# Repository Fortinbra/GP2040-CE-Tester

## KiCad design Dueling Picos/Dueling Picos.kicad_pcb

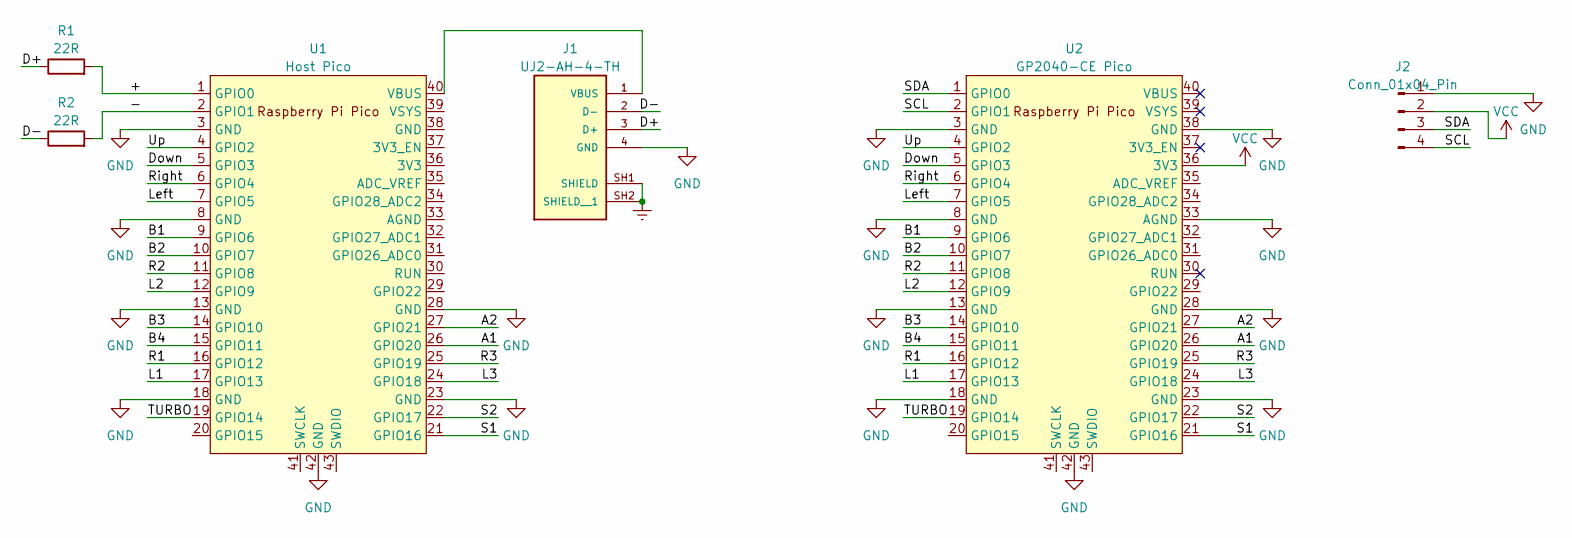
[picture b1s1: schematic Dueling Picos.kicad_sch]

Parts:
J1: UJ2-AH-4-TH; CUI_UJ2-AH-4-TH; PART_REV 1.0
J2: Conn_01x04_Pin; JST_SH_BM04B-SRSS-TB_1x04-1MP_P1.00mm_Vertical
R1, R2: 22R; R_0201_0603Metric
U1: Host Pico; RPi_Pico_SMD_TH
U2: GP2040-CE Pico; RPi_Pico_SMD_TH

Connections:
/+: R1.2, U1.1 (GPIO0)
/-: R2.2, U1.2 (GPIO1)
/A1: U1.26 (GPIO20), U2.26 (GPIO20)
/A2: U1.27 (GPIO21), U2.27 (GPIO21)
/B1: U1.9 (GPIO6), U2.9 (GPIO6)
/B2: U1.10 (GPIO7), U2.10 (GPIO7)
/B3: U1.14 (GPIO10), U2.14 (GPIO10)
/B4: U1.15 (GPIO11), U2.15 (GPIO11)
/D+: J1.3 (D+), R1.1
/D-: J1.2 (D-), R2.1
/Down: U1.5 (GPIO3), U2.5 (GPIO3)
/L1: U1.17 (GPIO13), U2.17 (GPIO13)
/L2: U1.12 (GPIO9), U2.12 (GPIO9)
/L3: U1.24 (GPIO18), U2.24 (GPIO18)
/Left: U1.7 (GPIO5), U2.7 (GPIO5)
/R1: U1.16 (GPIO12), U2.16 (GPIO12)
/R2: U1.11 (GPIO8), U2.11 (GPIO8)
/R3: U1.25 (GPIO19), U2.25 (GPIO19)
/Right: U1.6 (GPIO4), U2.6 (GPIO4)
/S1: U1.21 (GPIO16), U2.21 (GPIO16)
/S2: U1.22 (GPIO17), U2.22 (GPIO17)
/SCL: J2.4, U2.2 (GPIO1)
/SDA: J2.3, U2.1 (GPIO0)
/TURBO: U1.19 (GPIO14), U2.19 (GPIO14)
/Up: U1.4 (GPIO2), U2.4 (GPIO2)
Earth: J1.SH1 (SHIELD), J1.SH2 (SHIELD__1)
GND: J1.4 (GND), J2.1, U1.3 (GND), U1.8 (GND), U1.13 (GND), U1.18 (GND), U1.23 (GND), U1.28 (GND), U1.42 (GND), U2.3 (GND), U2.8 (GND), U2.13 (GND), U2.18 (GND), U2.23 (GND), U2.28 (GND), U2.33 (AGND), U2.38 (GND), U2.42 (GND)
unnamed: J1.1 (VBUS), U1.40 (VBUS)
VCC: J2.2, U2.36 (3V3)

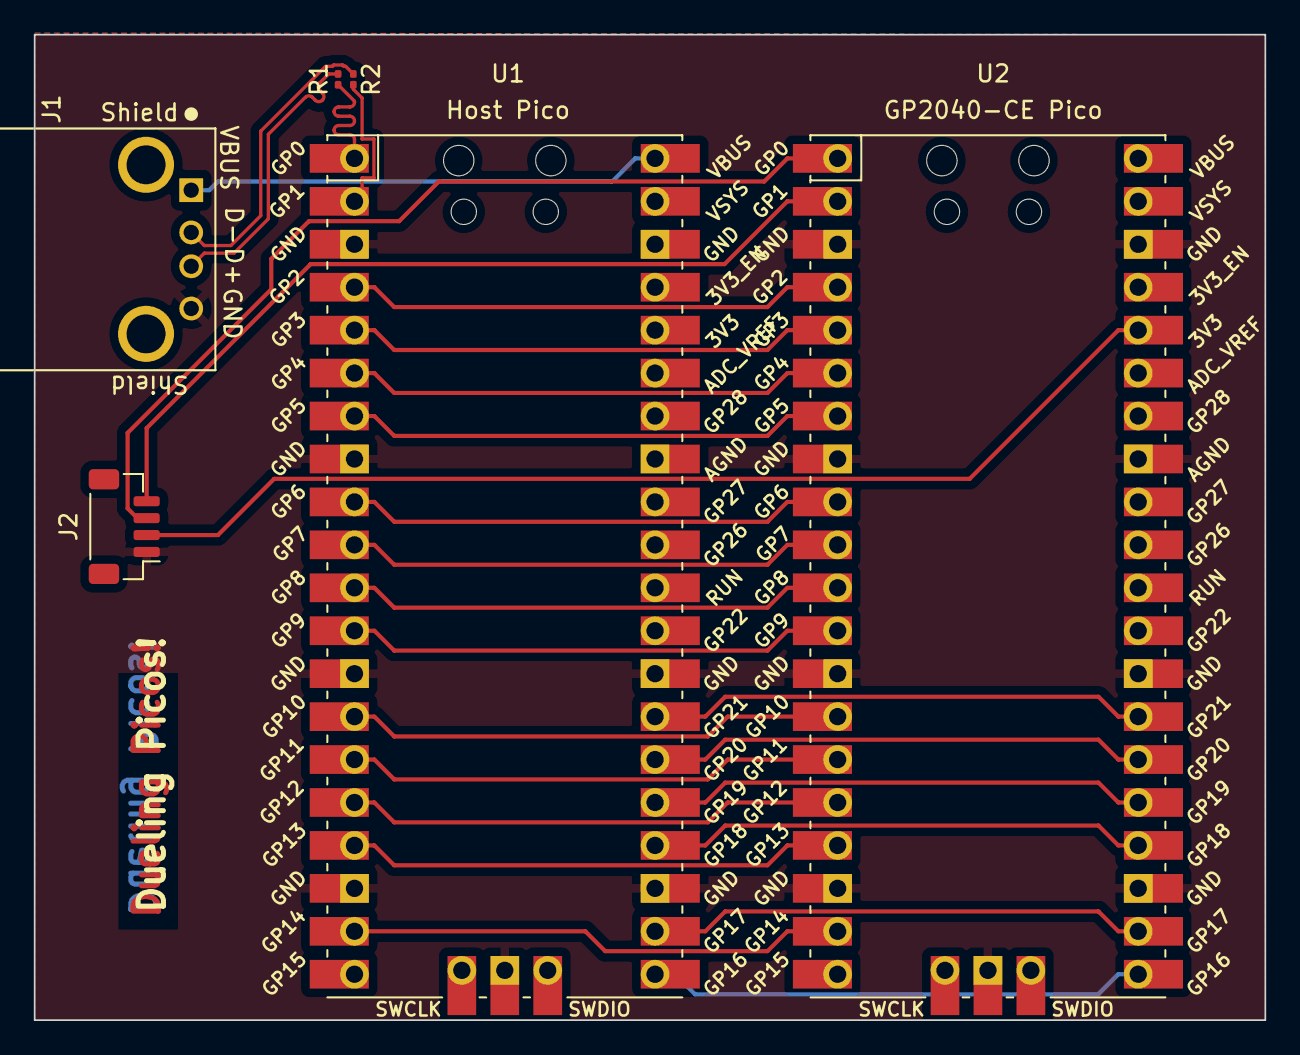
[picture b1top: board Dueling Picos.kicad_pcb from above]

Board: 2 copper layers, 72.8 x 58.3 mm, 6 parts (0 on the bottom side), 29 nets.

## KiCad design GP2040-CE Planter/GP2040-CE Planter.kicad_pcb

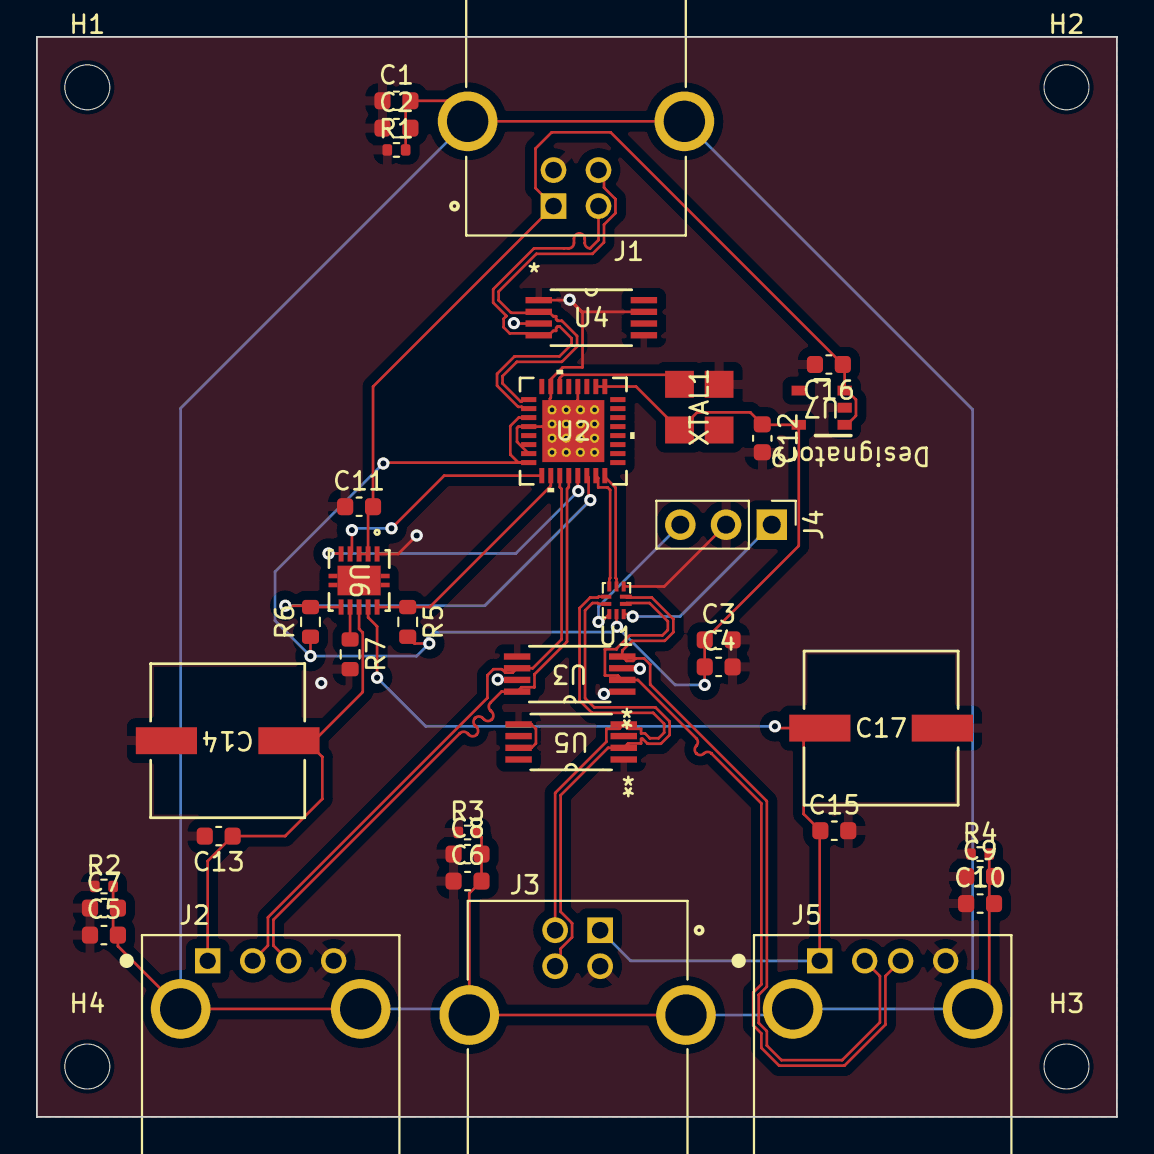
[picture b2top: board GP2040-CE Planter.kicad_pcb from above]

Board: 4 copper layers, 60.0 x 60.0 mm, 41 parts (0 on the bottom side), 24 nets.

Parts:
C1, C2, C3, C4, C5, C6, C7, C8, C9, C10, C11, C12, C13, C15, C16: C; C_0603_1608Metric
C14, C17: C_Polarized_Small; CAP_RHA&slash_HS_8X6P7_NCH
H1, H2, H3, H4: MountingHole; MountingHole_2.5mm
J1, J3: UJ2-BH-1-TH; CUI_UJ2-BH-1-TH
J2, J5: UJ2-AH-4-TH; CUI_UJ2-AH-4-TH
J4: Conn_01x03; PinHeader_1x03_P2.54mm_Vertical
R1, R2, R3, R4: R; R_0402_1005Metric
R5, R6, R7: R; R_0603_1608Metric
U1: TMUXHS221NKGR; TMUXHS221
U2: TUSB2046IBVF; RHB32_3P45X3P45_TEX
U3, U4, U5: SN75240PWR; SN75240
U6: TPS2561ADRCR; DRC10_2P4X1P65_TEX
U7: TLV73333PDBVR; TLV7333P
XTAL1: SIT1602BC-33-33E-6.000000T; SON4_SIT1602-3_SIT

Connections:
+3.3V: C3.1, C4.1, C12.1, R5.2, R6.1, U1.9 (VCC), U2.3 (VCC), U2.8 (BUSPWR), U2.25 (VCC), U2.26 (*EXTMEM), U7.5 (OUT), XTAL1.4 (VDD)
/DA+: U1.4 (DA-), U2.16 (DP2)
/DA-: U1.5 (DA+), U2.15 (DM2)
/DB+: J3.3 (D+), U1.7 (DB+), U5.2 (C)
/DB-: J3.2 (D-), U1.6 (DB-), U5.4 (D)
/DN_1_D+: J2.3 (D+), U2.12 (DP1), U3.8 (A)
/DN_1_D-: J2.2 (D-), U2.11 (DM1), U3.6 (B)
/DN_1_VBUS: C13.1, C14.1, J2.1 (VBUS), U6.8 (OUT2)
/DN_2_D+: J5.3 (D+), U1.1 (D+), U3.2 (C)
/DN_2_D-: J5.2 (D-), U1.2 (D-), U3.4 (D)
/DN_2_VBUS: C15.1, C17.1, J3.1 (VBUS), J5.1 (VBUS), U6.9 (OUT1)
/OEN: J4.3, U1.8 (OEN)
/OVERCUR1_N: R5.1, U2.10 (*OVRCUR1), U6.10 (*FAULT1)
/OVERCUR2_N: R6.2, U2.14 (*OVRCUR2), U6.6 (*FAULT2)
/PWRCTL1_BATEN1: U2.9 (*PWRON1), U6.4 (EN1)
/PWRCTL2_BATEN2: U2.13 (*PWRON2), U6.5 (EN2)
/SEL: J4.1, U1.10 (SEL)
/UP_D+: J1.3 (D+), U2.1 (DP0), U4.2 (C)
/UP_D-: J1.2 (D-), U2.2 (DM0), U4.4 (D)
/XI: U2.30 (XTAL1), XTAL1.3 (OUT)
Earth: C1.2, C2.2, C5.2, C6.2, C7.2, C8.2, C9.2, C10.2, J1.SH1 (SHIELD), J1.SH2 (SHIELD__1), J2.SH1 (SHIELD), J2.SH2 (SHIELD__1), J3.SH1 (SHIELD), J3.SH2 (SHIELD__1), J5.SH1 (SHIELD), J5.SH2 (SHIELD__1), R1.2, R2.2, R3.2, R4.2
GND: C1.1, C2.1, C3.2, C4.2, C5.1, C6.1, C7.1, C8.1, C9.1, C10.1, C11.1, C12.2, C13.2, C14.2, C15.2, C16.2, C17.2, J1.4 (GND), J2.4 (GND), J3.4 (GND), J4.2, J5.4 (GND), R1.1, R2.1, R3.1, R4.1, R7.2, U1.3 (GND), U2.4 (*RESET), U2.6 (EEDATA/GANGED), U2.7 (GND), U2.28 (GND), U2.31 (TSTMODE), U2.33 (EPAD), U3.1 (GND), U3.3 (GND), U3.5 (GND), U3.7 (GND), U4.1 (GND), U4.3 (GND), U4.5 (GND), U4.7 (GND), U5.1 (GND), U5.3 (GND), U5.5 (GND), U5.7 (GND), U6.1 (GND), U7.2 (GND), XTAL1.2 (GND)
unnamed: R7.1, U6.7 (ILIM)
VBUS: C11.2, C16.1, J1.1 (VBUS), U6.2 (IN), U6.3 (IN), U7.1 (IN), U7.3 (EN)

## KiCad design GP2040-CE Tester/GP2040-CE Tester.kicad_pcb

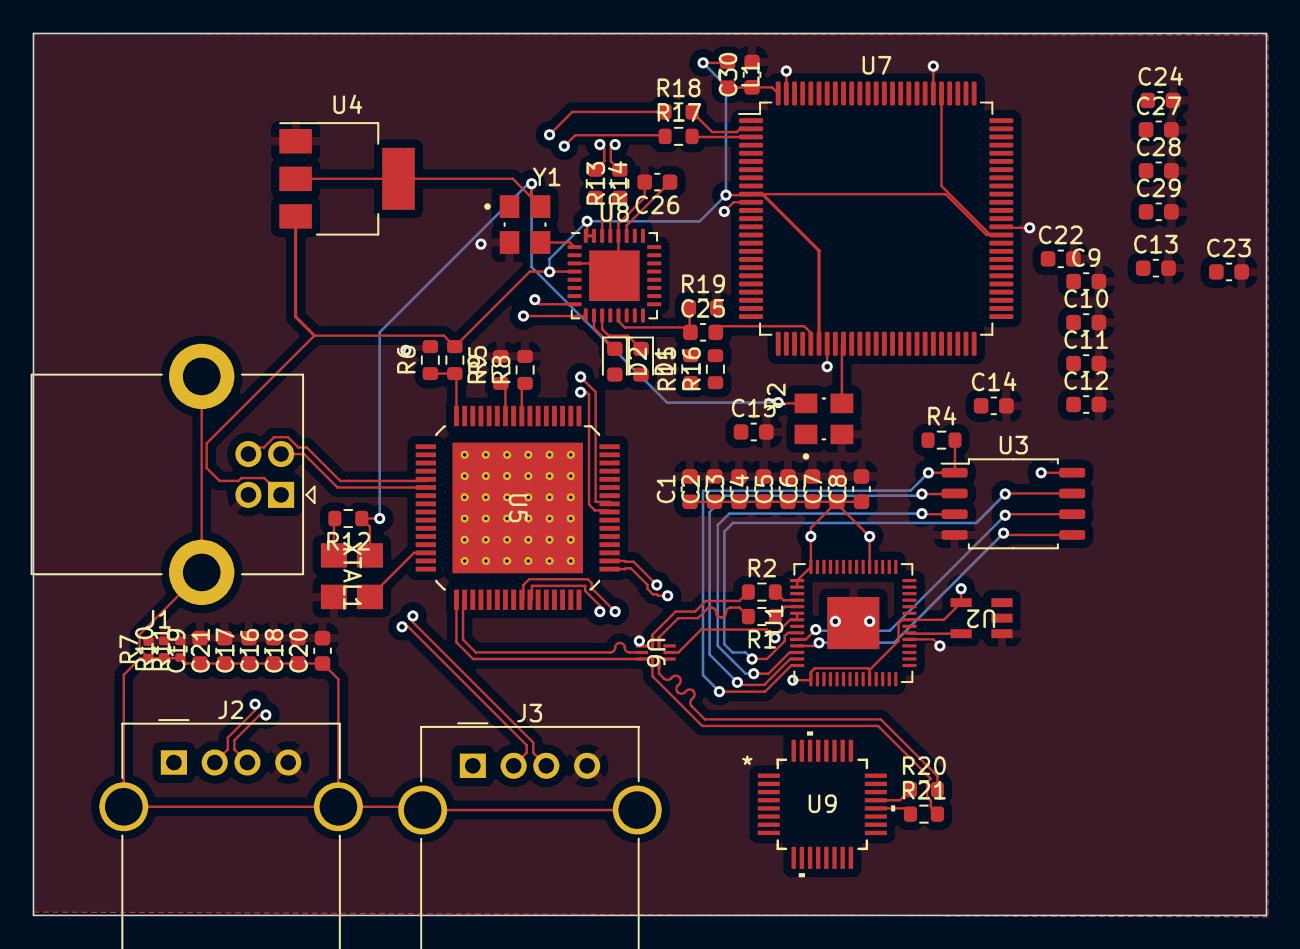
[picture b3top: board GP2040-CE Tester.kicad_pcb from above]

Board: 4 copper layers, 75.5 x 54.0 mm, 68 parts (0 on the bottom side), 51 nets.

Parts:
C1, C2, C3, C4, C5, C6, C7, C9, C10, C24, C25, C27, C28, C29, C30: 100nF; C_0603_1608Metric
C8, C11: 1uF; C_0603_1608Metric
C12: 100n; C_0603_1608Metric
C13, C14: 10uF; C_0603_1608Metric
C15: 10μF; C_0603_1608Metric
C16, C18, C20, C23: 0.1μF; C_0603_1608Metric
C17, C19, C21: 0.001μF; C_0603_1608Metric
C22, C26: 1μF; C_0603_1608Metric
D1, D2: LED; LED_0603_1608Metric
J1: USB_B; USB_B_Lumberg_2411_02_Horizontal
J2, J3: USB_A; USB_A_Molex_67643_Horizontal
L1: 10uH; L_0603_1608Metric
R1, R2: 24.7; R_0603_1608Metric
R4: 1k; R_0603_1608Metric
R5: 90.9KΩ 1%; R_0603_1608Metric
R6: 10KΩ 1%; R_0603_1608Metric
R7, R10, R11: 10KΩ 1%; R_0402_1005Metric
R8, R9: 4.7KΩ; R_0603_1608Metric
R12: 1KΩ; R_0603_1608Metric
R13, R14, R20, R21: 22R; R_0603_1608Metric
R15, R16, R17, R18, R19: 1K; R_0603_1608Metric
U1: RP2040; QFN-56-1EP_7x7mm_P0.4mm_EP3.2x3.2mm
U2: SIT2018BE-S8-33N-12.000000G; SiT1630-S
U3: W25Q128JVS; SOIC-8_5.23x5.23mm_P1.27mm
U4: NCP1117-3.3_SOT223; SOT-223-3_TabPin2
U5: TUSB4041IPAPR; TUSB4041I-Q1
U6: PTMUXHS221NKGR; TMUXHS221N
U7: ATmega2560-16A; TQFP-100_14x14mm_P0.5mm
U8: ATmega16U2-M; QFN-32-1EP_5x5mm_P0.5mm_EP3.1x3.1mm
U9: MAX3421EEHJ+T
XTAL1: SIT1602AC-33-33E-24.000000Y; SIT1602
Y1, Y2: SIT9003AC-24-33ED-16.00000T

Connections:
+1V1: C9.1, C10.1, C11.1, U1.23 (DVDD), U1.45 (VREG_VOUT), U1.50 (DVDD)
+3.3V: C1.1, C2.1, C3.1, C4.1, C5.1, C6.1, C7.1, C8.1, C12.1, C14.1, C22.1, C23.1, R12.1, U1.1 (IOVDD), U1.10 (IOVDD), U1.22 (IOVDD), U1.33 (IOVDD), U1.42 (IOVDD), U1.43 (ADC_AVDD), U1.44 (VREG_IN), U1.48 (USB_VDD), U1.49 (IOVDD), U2.4 (VDD), U3.8 (VCC), U4.2 (VO), U6.9 (VCC), XTAL1.4 (VDD), Y1.4 (VDD), Y2.4 (VDD)
+5V: C13.1, C15.1, C24.1, C27.1, C28.1, C29.1, J1.1 (VBUS), L1.1, R5.1, R15.2, R16.2, U4.3 (VI), U7.10 (VCC), U7.31 (VCC), U7.61 (VCC), U7.80 (VCC), U8.4 (VCC), U8.31 (UVCC), U8.32 (AVCC)
/RPUSBD+: R1.2, U6.1 (D+)
/RPUSBD-: R2.1, U6.2 (D-)
/Sheetname: Embeded RP2040/CLK: U1.20 (XIN), U2.5 (OUT)
/Sheetname: Embeded RP2040/LD+: R1.1, U1.47 (USB_DP)
/Sheetname: Embeded RP2040/LD-: R2.2, U1.46 (USB_DM)
/Sheetname: Embeded RP2040/QSPI_SCLK: U1.52 (QSPI_SCLK), U3.6 (CLK)
/Sheetname: Embeded RP2040/QSPI_SD0: U1.53 (QSPI_SD0), U3.5 (DI(IO0))
/Sheetname: Embeded RP2040/QSPI_SD1: U1.55 (QSPI_SD1), U3.2 (DO(IO1))
/Sheetname: Embeded RP2040/QSPI_SD2: U1.54 (QSPI_SD2), U3.3 (IO2)
/Sheetname: Embeded RP2040/QSPI_SD3: U1.51 (QSPI_SD3), U3.7 (IO3)
/Sheetname: Embeded RP2040/QSPI_SS: R4.2, U1.56 (QSPI_SS), U3.1 (~CS)
/Sheetname: Mega2560/AVCC: C30.1, L1.2, U7.100 (AVCC)
/Sheetname: Mega2560/MEGA_USB_D+: R13.2, U5.41 (USB_DP_DN2)
/Sheetname: Mega2560/MEGA_USB_D-: R14.1, U5.42 (USB_DM_DN2)
/Sheetname: Mega2560/PE0: R18.2, U7.2 (PE0)
/Sheetname: Mega2560/PE1: R17.2, U7.3 (PE1)
/Sheetname: Mega2560/RESET: C25.2, U7.30 (~RESET)
/Sheetname: Mega2560/RXL: D2.1 (K), U8.10 (PD4)
/Sheetname: Mega2560/SHIELDUSBD+: R20.2, U6.7 (DB+)
/Sheetname: Mega2560/SHIELDUSBD-: R21.2, U6.6 (DB-)
/Sheetname: Mega2560/TXL: D1.1 (K), U8.11 (PD5)
/Sheetname: USB Hub/CLK: U5.30 (XI), XTAL1.3 (OUT)
/Sheetname: USB Hub/UPSD+: J1.3 (D+), U5.21 (USB_DP_UP)
/Sheetname: USB Hub/UPSD-: J1.2 (D-), U5.22 (USB_DM_UP)
/Sheetname: USB Hub/USB_3_D+: J2.3 (D+), U5.49 (USB_DP_DN3)
/Sheetname: USB Hub/USB_3_D-: J2.2 (D-), U5.50 (USB_DM_DN3)
/Sheetname: USB Hub/USB_4_D+: J3.3 (D+), U5.56 (USB_DP_DN4)
/Sheetname: USB Hub/USB_4_D-: J3.2 (D-), U5.57 (USB_DM_DN4)
/USBAD+: U5.33 (USB_DP_DN1), U6.5 (DA+)
/USBAD-: U5.34 (USB_DM_DN1), U6.4 (DA-)
Earth: C16.1, C17.1, C18.1, C19.1, C20.1, C21.1, J1.5 (Shield), J2.5 (Shield), J3.5 (Shield), R7.1, R10.1, R11.1
GND: C1.2, C2.2, C3.2, C4.2, C5.2, C6.2, C7.2, C8.2, C9.2, C10.2, C11.2, C12.2, C13.2, C14.2, C15.2, C16.2, C17.2, C18.2, C19.2, C20.2, C21.2, C22.2, C23.2, C24.2, C26.2, C27.2, C28.2, C29.2, C30.2, J1.4 (GND), J2.4 (GND), J3.4 (GND), R6.2, R7.2, R8.2, R9.2, R10.2, R11.2, R19.2, U1.19 (TESTEN), U1.57 (GND), U2.1 (GND), U3.4 (GND), U4.1 (GND), U6.3 (GND), U7.11 (GND), U7.32 (GND), U7.62 (GND), U7.81 (GND), U7.99 (GND), U8.3 (GND), U8.28 (UGND), U8.33 (GND), XTAL1.2 (GND), Y1.2 (GND), Y2.2 (GND)
unnamed: D1.2 (A), R15.1
unnamed: D2.2 (A), R16.1
unnamed: R8.1, U5.8 (FULLPWRMGMT_SMBA1_N)
unnamed: R9.1, U5.10 (GANGED_SMBA2_HS_UP)
unnamed: R5.2, R6.1, U5.16 (USB_VBUS)
unnamed: U7.34 (XTAL1), Y2.3 (CLK)
unnamed: R13.1, U8.29 (D+)
unnamed: R14.2, U8.30 (D-)
unnamed: R17.1, U8.8 (PD2)
unnamed: R18.1, U8.9 (PD3)
unnamed: C26.1, U8.27 (UCAP)
unnamed: U8.1 (XTAL1), Y1.3 (CLK)
unnamed: C25.1, R19.1, U8.13 (~HWB/PD7)
unnamed: R20.1, U9.21 (D+)
unnamed: R21.1, U9.20 (D-)
unnamed: R12.2, XTAL1.1 (OE/ST)

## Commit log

2023-04-16 adding most of the components, and schematic connections
2023-04-16 Syncing
2023-04-17 Building a garden
2023-04-18 Replacing out of stock with instock components
2023-04-22 ERC passes
2023-04-27 Dueling Picos!
